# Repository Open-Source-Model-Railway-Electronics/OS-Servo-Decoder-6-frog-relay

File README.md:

# OS-Servo-Decoder-6-frog-relay

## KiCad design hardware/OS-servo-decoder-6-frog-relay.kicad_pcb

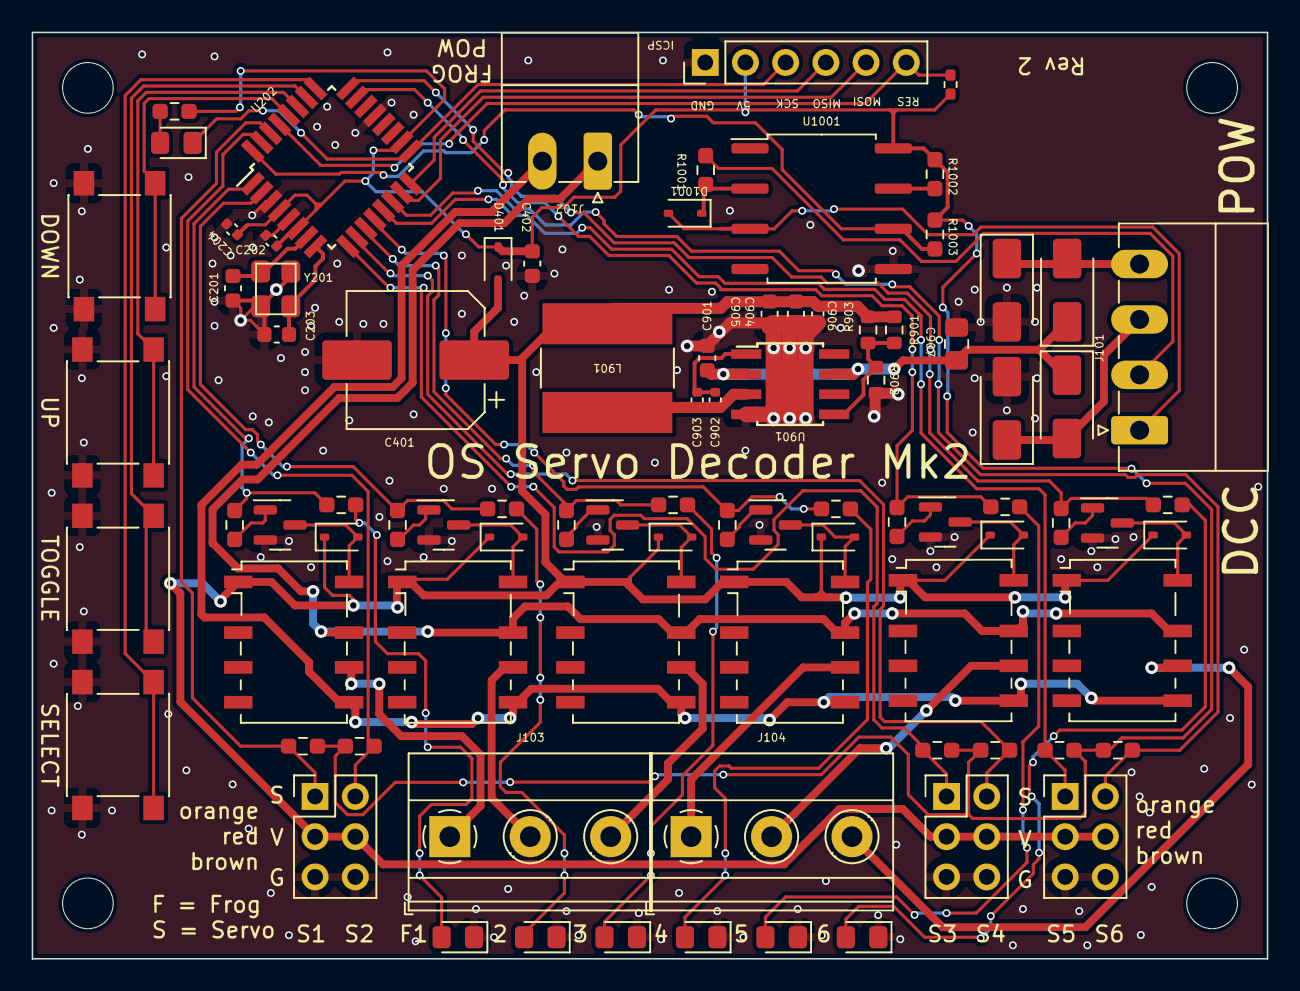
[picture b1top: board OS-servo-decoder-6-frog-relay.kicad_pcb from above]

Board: 2 copper layers, 78.0 x 58.5 mm, 87 parts (0 on the bottom side), 63 nets.

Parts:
C201, C203: 12pF; C_0603_1608Metric
C202, C204, C902, C906: 100nF; C_0402_1005Metric
C401: 1000uF; CP_Elec_8x10.5
C402, C901, C904, C905: 22uF; C_0603_1608Metric
C903: 22nF; C_0402_1005Metric
C907: 100nF; C_0805_2012Metric_Pad1.18x1.45mm_HandSolder
D201, D601, D602, D703, D704, D803, D804: LED; LED_0805_2012Metric_Pad1.15x1.40mm_HandSolder
D401, D701, D702, D801, D802, D901, D902, D1001: 1N4148WS; D_SOD-323
D1101, D1102, D1103, D1104: SS53; D_SMA
J101: Screw_Terminal_01x04; PhoenixContact_MC_1,5_4-G-3.5_1x04_P3.50mm_Horizontal
J102: Screw_Terminal_01x02; PhoenixContact_MC_1,5_2-G-3.5_1x02_P3.50mm_Horizontal
J103, J104: Screw_Terminal_01x03; TerminalBlock_Phoenix_MKDS-1,5-3-5.08_1x03_P5.08mm_Horizont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
J201: ICSP; PinHeader_1x06_P2.54mm_Vertical
J701, J801, J901: Conn_02x03_Odd_Even; PinHeader_2x03_P2.54mm_Vertical
K701, K702, K801, K802, K901, K902: G6K-2F-Y-TR DC5; Relay_DPDT_Omron_G6K-2F-Y
L901: L; L_Bourns-SRN8040_8x8.15mm
Q701, Q702, Q801, Q802, Q901, Q902: NPN_TOR; SOT-23
R201: 6k2; R_0603_1608Metric_Pad0.98x0.95mm_HandSolder
R202: 10k; R_0402_1005Metric_Pad0.72x0.64mm_HandSolder
R601, R602, R705, R706, R805, R806: 6k8; R_0603_smalltext
R701, R702, R801, R802, R904, R905, R1002, R1003: 10k; R_0603_smalltext
R703, R704, R803, R804, R906, R907: 1k5; R_0603_smalltext
R901: 220k; R_0603_1608Metric
R902: 20k; R_0603_1608Metric
R903: 150k; R_0603_1608Metric
R1001: 1k; R_0603_smalltext
SW601, SW602, SW603, SW604: SW_Push; tactile_SMD_6mm
U202: ATmega328-A; TQFP-32_7x7mm_P0.8mm
U901: MT2499A; TI_SO-PowerPAD-8
U1001: 6N137; SOP-8_6.62x9.15mm_P2.54mm
Y201: Crystal_GND2; crystal_arduino

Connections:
+5V: C202.1, C204.1, C402.1, D401.1 (K), J201.2, R201.1, R202.2, R701.2, R702.2, R801.2, R802.2, R904.2, R905.2, R1002.1, R1003.1, U202.4 (VCC), U202.6 (VCC), U202.18 (AVCC), U1001.8 (VCC)
+5VA: C401.1, C904.1, C905.1, C906.1, D401.2 (A), D701.1 (K), D702.1 (K), D801.1 (K), D802.1 (K), D901.1 (K), D902.1 (K), J701.3, J701.4, J801.3, J801.4, J901.3, J901.4, K701.1, K702.1, K801.1, K802.1, K901.1, K902.1, L901.2, R901.1, R903.2
/DCC/DCC_A: J101.2, R1001.1
/DCC/DCC_B: D1001.2 (A), J101.1, U1001.3 (C)
/DCC/DCC_TTL: R1003.2, U202.32 (PD2), U1001.6 (VO)
/D_bridge/AC_1: D1101.2 (A), D1102.1 (K), J101.4
/D_bridge/AC_2: D1103.2 (A), D1104.1 (K), J101.3
/atmega/LED: D201.1 (K), J201.3, U202.17 (PB5)
/atmega/MISO: J201.4, U202.16 (PB4)
/atmega/MOSI: J201.5, U202.15 (PB3)
/atmega/X1: C201.2, U202.7 (XTAL1/PB6), Y201.1
/atmega/X2: C203.2, U202.8 (XTAL2/PB7), Y201.3
/atmega/bus1.pin1: J701.1, R701.1, U202.30 (PD0)
/atmega/bus1.pin2: J701.2, R702.1, U202.31 (PD1)
/atmega/bus1.relay1: R601.2, R703.2, U202.1 (PD3)
/atmega/bus1.relay2: R602.2, R704.2, U202.2 (PD4)
/atmega/bus2.pin1: J801.1, R801.1, U202.9 (PD5)
/atmega/bus2.pin2: J801.2, R802.1, U202.10 (PD6)
/atmega/bus2.relay1: R705.2, R803.2, U202.11 (PD7)
/atmega/bus2.relay2: R706.2, R804.2, U202.12 (PB0)
/atmega/bus3.pin1: J901.1, R904.1, U202.13 (PB1)
/atmega/bus3.pin2: J901.2, R905.1, U202.14 (PB2)
/atmega/bus3.relay1: R805.2, R906.2, U202.23 (PC0)
/atmega/bus3.relay2: R806.2, R907.2, U202.24 (PC1)
/atmega/reset: J201.6, R202.1, U202.29 (~RESET/PC6)
/atmega/sw1: SW601.2, U202.25 (PC2)
/atmega/sw2: SW602.2, U202.26 (PC3)
/atmega/sw3: SW603.2, U202.27 (PC4)
/atmega/sw4: SW604.2, U202.28 (PC5)
/servo1-2/DCC_A: J102.2, K701.5, K702.5, K801.5, K802.5, K901.5, K902.5
/servo1-2/DCC_B: J102.1, K701.7, K702.7, K801.7, K802.7, K901.7, K902.7
/servo1-2/FROG1: J103.1, K701.6
/servo1-2/FROG2: J103.2, K702.6
/servo3-4/FROG1: J103.3, K801.6
/servo3-4/FROG2: J104.1, K802.6
/servo5-6/FROG1: J104.2, K901.6
/servo5-6/FROG2: J104.3, K902.6
GND: C201.1, C202.2, C203.1, C204.2, C401.2, C402.2, C901.2, C904.2, C905.2, C906.2, C907.1, D601.1 (K), D602.1 (K), D703.1 (K), D704.1 (K), D803.1 (K), D804.1 (K), D1102.2 (A), D1104.2 (A), J201.1, J701.5, J701.6, J801.5, J801.6, J901.5, J901.6, Q701.2 (E), Q702.2 (E), Q801.2 (E), Q802.2 (E), Q901.2 (E), Q902.2 (E), R902.2, SW601.1, SW602.1, SW603.1, SW604.1, U202.3 (GND), U202.5 (GND), U202.21 (GND), U901.4 (GND), U901.9 (GND), U1001.5 (GND), Y201.2 (GND), Y201.4 (GND)
unnamed: D201.2 (A), R201.2
unnamed: D601.2 (A), R601.1
unnamed: D602.2 (A), R602.1
unnamed: D701.2 (A), K701.8, Q701.3 (C)
unnamed: D702.2 (A), K702.8, Q702.3 (C)
unnamed: D703.2 (A), R705.1
unnamed: D704.2 (A), R706.1
unnamed: D801.2 (A), K801.8, Q801.3 (C)
unnamed: D802.2 (A), K802.8, Q802.3 (C)
unnamed: D803.2 (A), R805.1
unnamed: D804.2 (A), R806.1
unnamed: D901.2 (A), K901.8, Q901.3 (C)
unnamed: D902.2 (A), K902.8, Q902.3 (C)
unnamed: D1001.1 (K), R1001.2, U1001.2 (A)
unnamed: Q701.1 (B), R703.1
unnamed: Q702.1 (B), R704.1
unnamed: Q801.1 (B), R803.1
unnamed: Q802.1 (B), R804.1
unnamed: Q901.1 (B), R906.1
unnamed: Q902.1 (B), R907.1
unnamed: C902.1, C903.1, U901.1 (BS)
unnamed: R901.2, R902.1, R903.1, U901.5 (FB)
unnamed: C902.2, C903.2, L901.1, U901.3 (SW)
unnamed: R1002.2, U1001.7 (EN)
VCC: C901.1, C907.2, D1101.1 (K), D1103.1 (K), U901.2 (Vin), U901.7 (EN)

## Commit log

2025-06-13 added initial files
2025-06-15 minor to change to PCB
2025-06-17 added or renamed PNG preview
2025-06-18 deleted source code in favor of sub module
2025-06-18 Cleanup failed submodule attempt for software
2025-06-18 Added submodule OS-Servo-Decoder-Core as software/
2025-06-19 Toegevoegd: handleiding (manual.odt)
2025-06-19 Hersteld: handleiding toegevoegd in docs/
